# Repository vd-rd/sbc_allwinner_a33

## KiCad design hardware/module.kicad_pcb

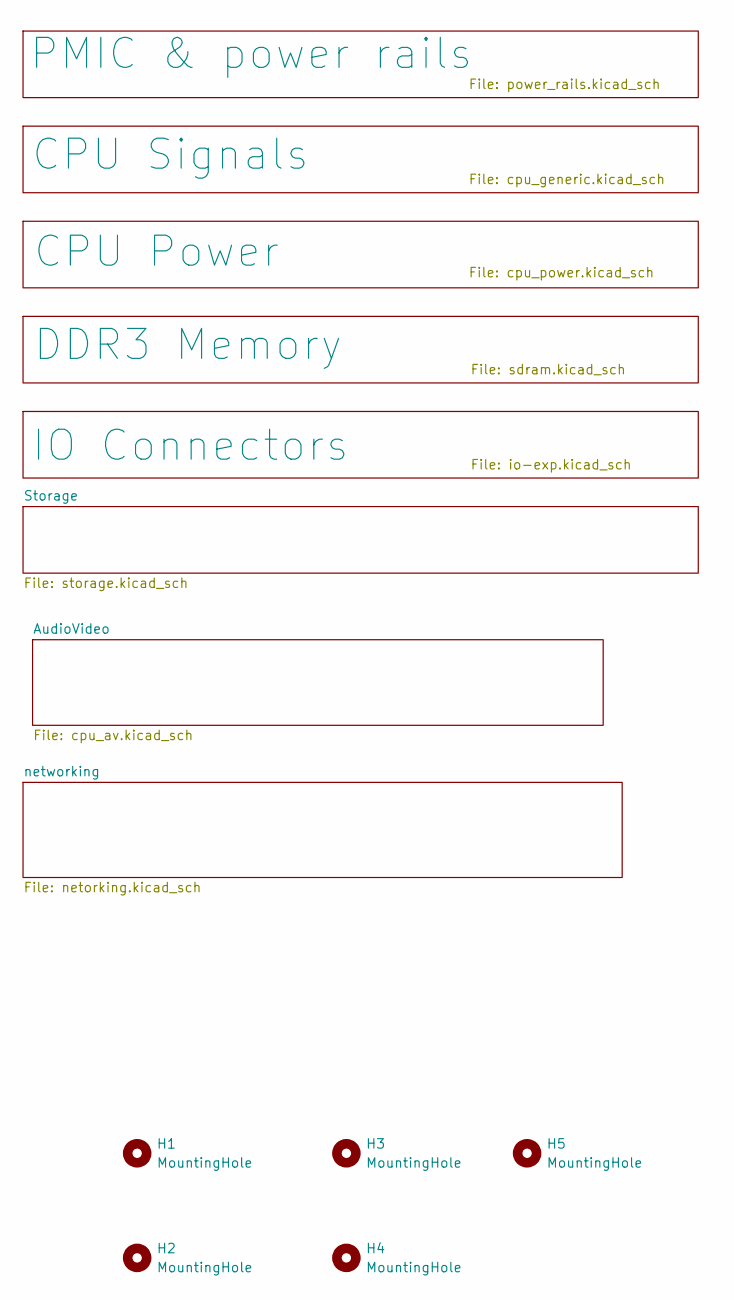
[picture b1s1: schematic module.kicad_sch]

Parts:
H1, H2, H3, H4, H5: MountingHole; MountingHole_2.7mm_M2.5_DIN965

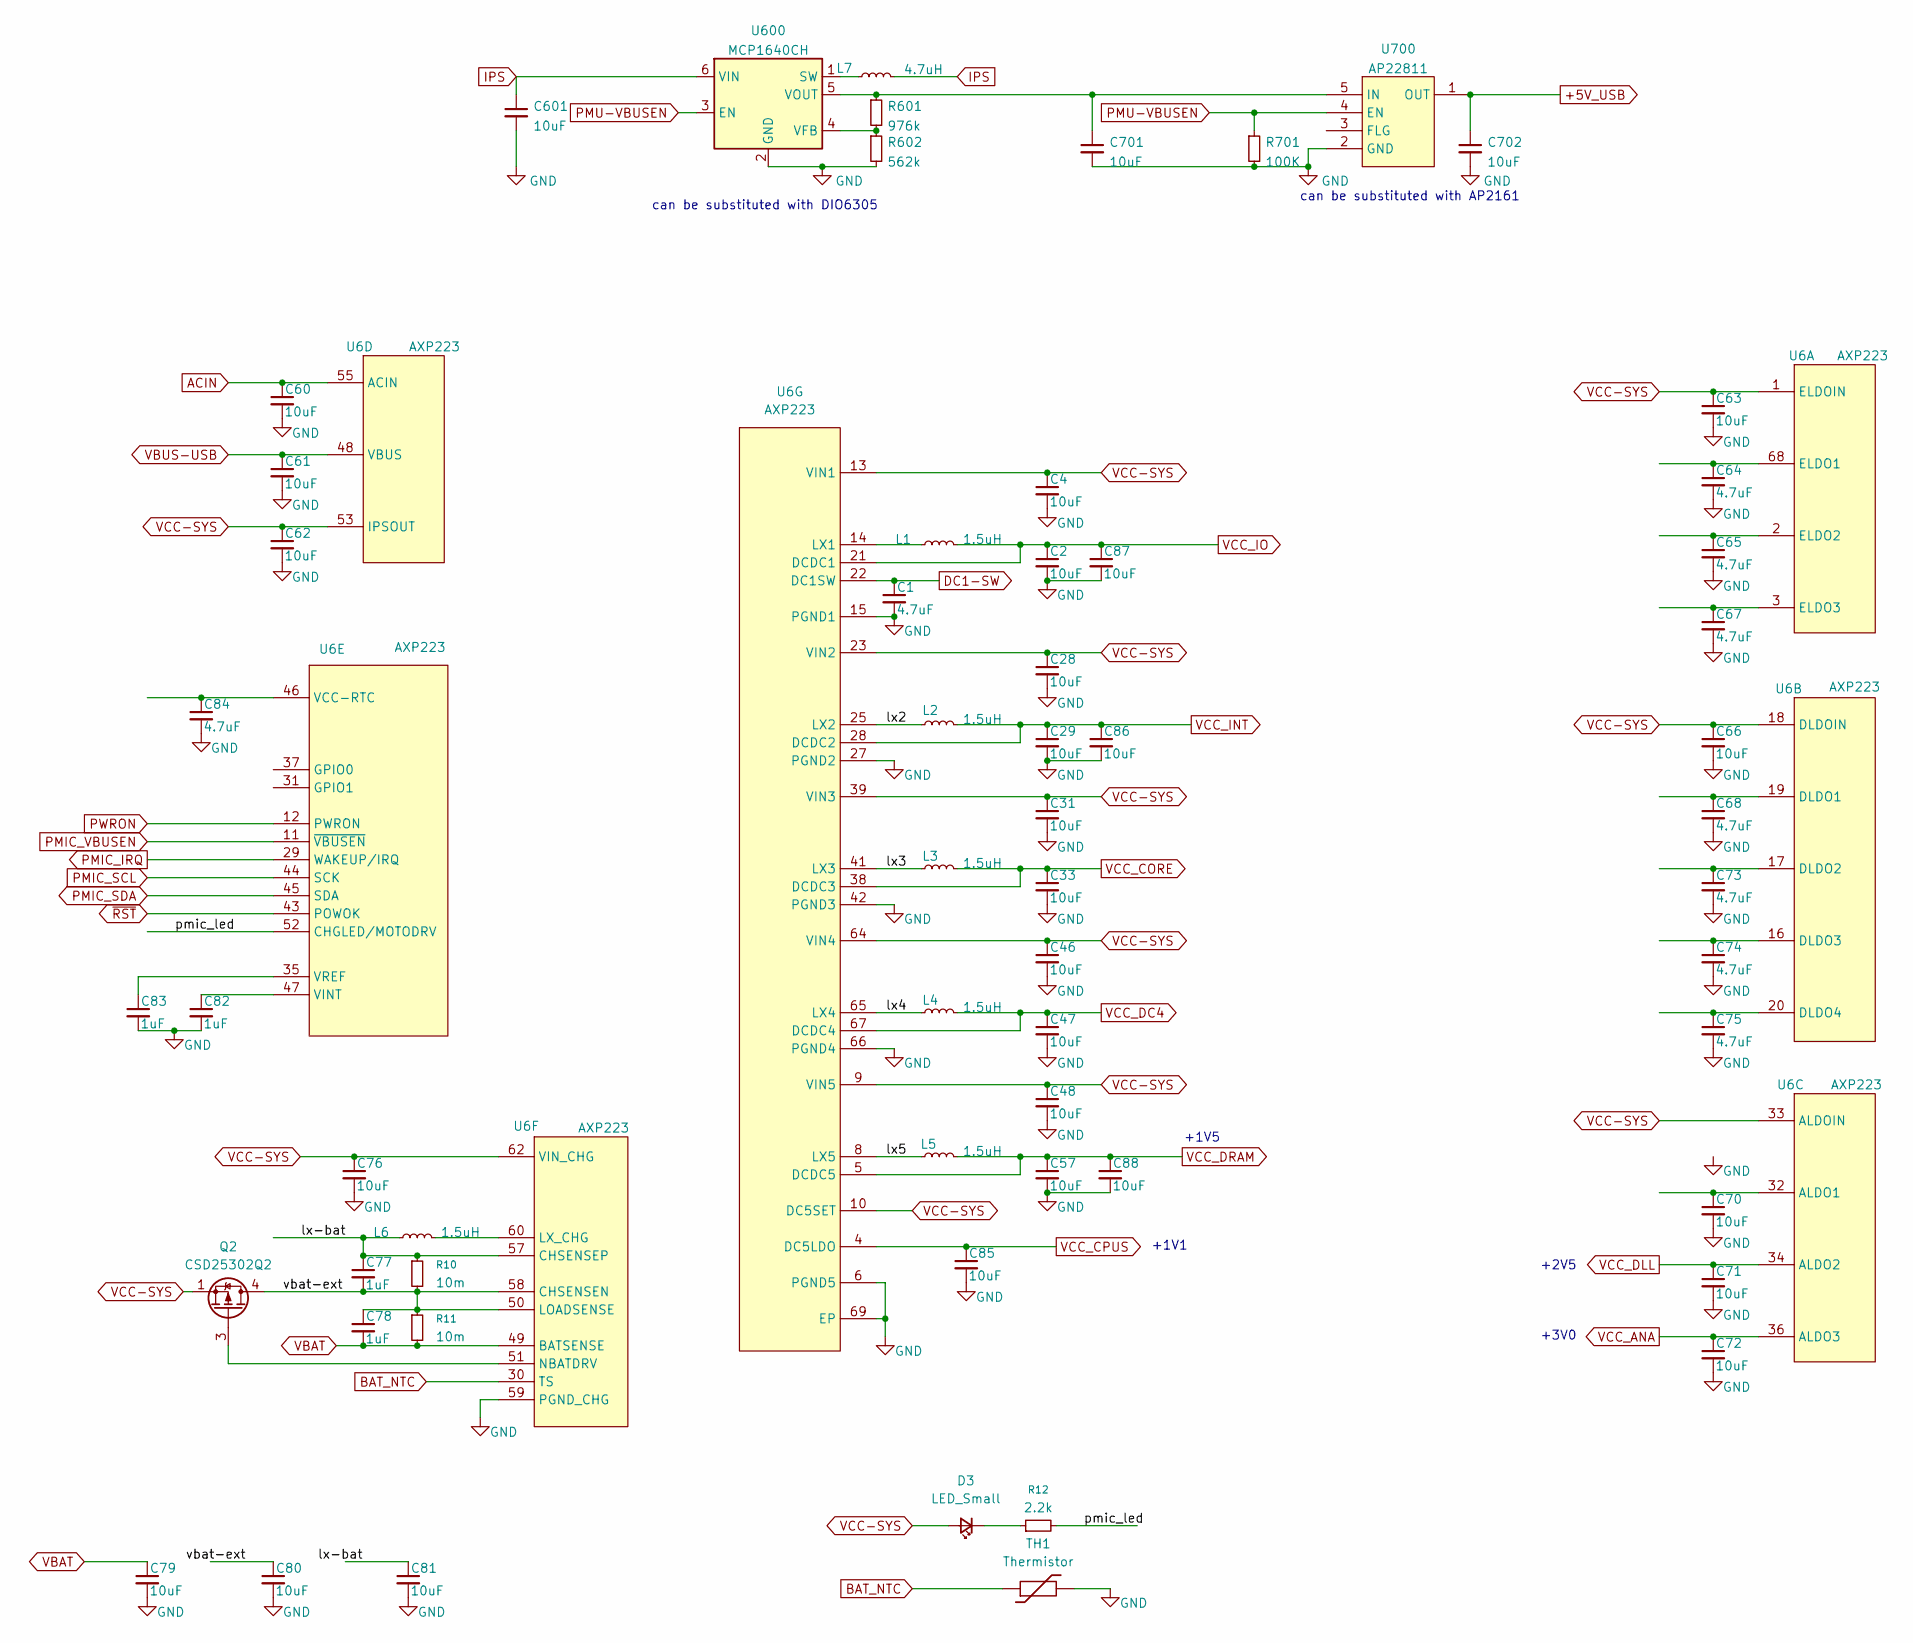
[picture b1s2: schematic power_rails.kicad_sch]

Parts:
C1, C64, C65, C67, C68, C73, C74, C75, C84: 4.7uF; C_0402_1005Metric
C2, C4, C28, C29, C31, C33, C46, C47, C48, C57, C60, C61, C62, C63, C66, C70, C71, C72, C76, C79, C80, C81, C85, C86, C87, C88, C601, C701, C702: 10uF; C_0603_1608Metric
C77, C78, C82, C83: 1uF; C_0402_1005Metric
D3: LED_Small; LED_0603_1608Metric
L1, L2, L3, L4, L5, L6: 1.5uH; L_APV_ANR252010
L7: 4.7uH; L_Wuerth_MAPI-2510
Q2: CSD25302Q2; Texas_DQK
R10, R11: 10m; R_0805_2012Metric
R12: 2.2k; R_0402_1005Metric
R601: 976k; R_0402_1005Metric
R602: 562k; R_0402_1005Metric
R701: 100K; R_0402_1005Metric
TH1: Thermistor; R_0603_1608Metric
U6: AXP223; QFN-68-1EP_8x8mm_P0.4mm_EP5.5x5.5mm_ThermalVias
U600: MCP1640CH; SOT-23-6
U700: AP22811; SOT-23-5

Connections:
+5V_USB: C702.1, U700.1 (OUT); also elsewhere on the board
/PMIC & power rails/lx2: L2.1, U6.24 (LX2), U6.25 (LX2)
/PMIC & power rails/lx3: L3.1, U6.40 (LX3), U6.41 (LX3)
/PMIC & power rails/lx4: L4.1, U6.65 (LX4)
/PMIC & power rails/lx5: L5.1, U6.7 (LX5), U6.8 (LX5)
/PMIC & power rails/lx-bat: C77.1, C81.1, L6.1, R10.1, U6.57 (CHSENSEP)
/PMIC & power rails/pmic_led: R12.2, U6.52 (CHGLED/MOTODRV)
/PMIC & power rails/vbat-ext: C77.2, C78.1, C80.1, Q2.4 (D), Q2.7 (D), R10.2, R11.1, U6.50 (LOADSENSE), U6.58 (CHSENSEN)
ACIN: C60.1, U6.55 (ACIN), U6.56 (ACIN); also elsewhere on the board
BAT_NTC: TH1.1, U6.30 (TS); also elsewhere on the board
DC1-SW: C1.1, U6.22 (DC1SW)
GND: C1.2, C2.2, C4.2, C28.2, C29.2, C31.2, C33.2, C46.2, C47.2, C48.2, C57.2, C60.2, C61.2, C62.2, C63.2, C64.2, C65.2, C66.2, C67.2, C68.2, C70.2, C71.2, C72.2, C73.2, C74.2, C75.2, C76.2, C79.2, C80.2, C81.2, C82.2, C83.2, C84.2, C85.2, C86.2, C87.2, C88.2, C601.2, C701.2, C702.2, R602.2, R701.2, TH1.2, U6.6 (PGND5), U6.15 (PGND1), U6.26 (PGND2), U6.27 (PGND2), U6.42 (PGND3), U6.59 (PGND_CHG), U6.66 (PGND4), U6.69 (EP), U600.2 (GND), U700.2 (GND); also elsewhere on the board
IPS: C601.1, L7.2, U600.6 (VIN)
unnamed: D3.1 (K), R12.1
unnamed: L6.2, U6.60 (LX_CHG), U6.61 (LX_CHG)
unnamed: Q2.3 (G), U6.51 (NBATDRV)
unnamed: C64.1, U6.68 (ELDO1)
unnamed: C65.1, U6.2 (ELDO2)
unnamed: C67.1, U6.3 (ELDO3)
unnamed: C68.1, U6.19 (DLDO1)
unnamed: C73.1, U6.17 (DLDO2)
unnamed: C74.1, U6.16 (DLDO3)
unnamed: C75.1, U6.20 (DLDO4)
unnamed: C70.1, U6.32 (ALDO1)
unnamed: C84.1, U6.46 (VCC-RTC)
unnamed: C82.1, U6.47 (VINT)
unnamed: C83.1, U6.35 (VREF)
unnamed: L1.1, U6.14 (LX1)
unnamed: L7.1, U600.1 (SW)
unnamed: R601.2, R602.1, U600.4 (VFB)
unnamed: C701.1, R601.1, U600.5 (VOUT), U700.5 (IN)
PMIC_IRQ: U6.29 (WAKEUP/IRQ); also elsewhere on the board
PMIC_SCL: U6.44 (SCK); also elsewhere on the board
PMIC_SDA: U6.45 (SDA); also elsewhere on the board
PMIC_VBUSEN: U6.11 (~VBUSEN)
PMU-VBUSEN: R701.1, U600.3 (EN), U700.4 (EN)
PWRON: U6.12 (PWRON); also elsewhere on the board
VBAT: C78.2, C79.1, R11.2, U6.49 (BATSENSE); also elsewhere on the board
VBUS-USB: C61.1, U6.48 (VBUS)
VCC-SYS: C4.1, C28.1, C31.1, C46.1, C48.1, C62.1, C63.1, C66.1, C76.1, D3.2 (A), Q2.1 (S), Q2.2 (S), Q2.5 (S), Q2.6 (S), Q2.8 (S), U6.1 (ELDOIN), U6.9 (VIN5), U6.10 (DC5SET), U6.13 (VIN1), U6.18 (DLDOIN), U6.23 (VIN2), U6.33 (ALDOIN), U6.39 (VIN3), U6.53 (IPSOUT), U6.54 (IPSOUT), U6.62 (VIN_CHG), U6.63 (VIN_CHG), U6.64 (VIN4)
VCC_ANA: C72.1, U6.36 (ALDO3); also elsewhere on the board
VCC_CORE: C33.1, L3.2, U6.38 (DCDC3); also elsewhere on the board
VCC_CPUS: C85.1, U6.4 (DC5LDO); also elsewhere on the board
VCC_DC4: C47.1, L4.2, U6.67 (DCDC4)
VCC_DLL: C71.1, U6.34 (ALDO2); also elsewhere on the board
VCC_DRAM: C57.1, C88.1, L5.2, U6.5 (DCDC5); also elsewhere on the board
VCC_INT: C29.1, C86.1, L2.2, U6.28 (DCDC2); also elsewhere on the board
VCC_IO: C2.1, C87.1, L1.2, U6.21 (DCDC1); also elsewhere on the board
~RST: U6.43 (POWOK); also elsewhere on the board

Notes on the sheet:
can be substituted with DIO6305
can be substituted with AP2161
+1V1
+2V5
+1V5
+3V0

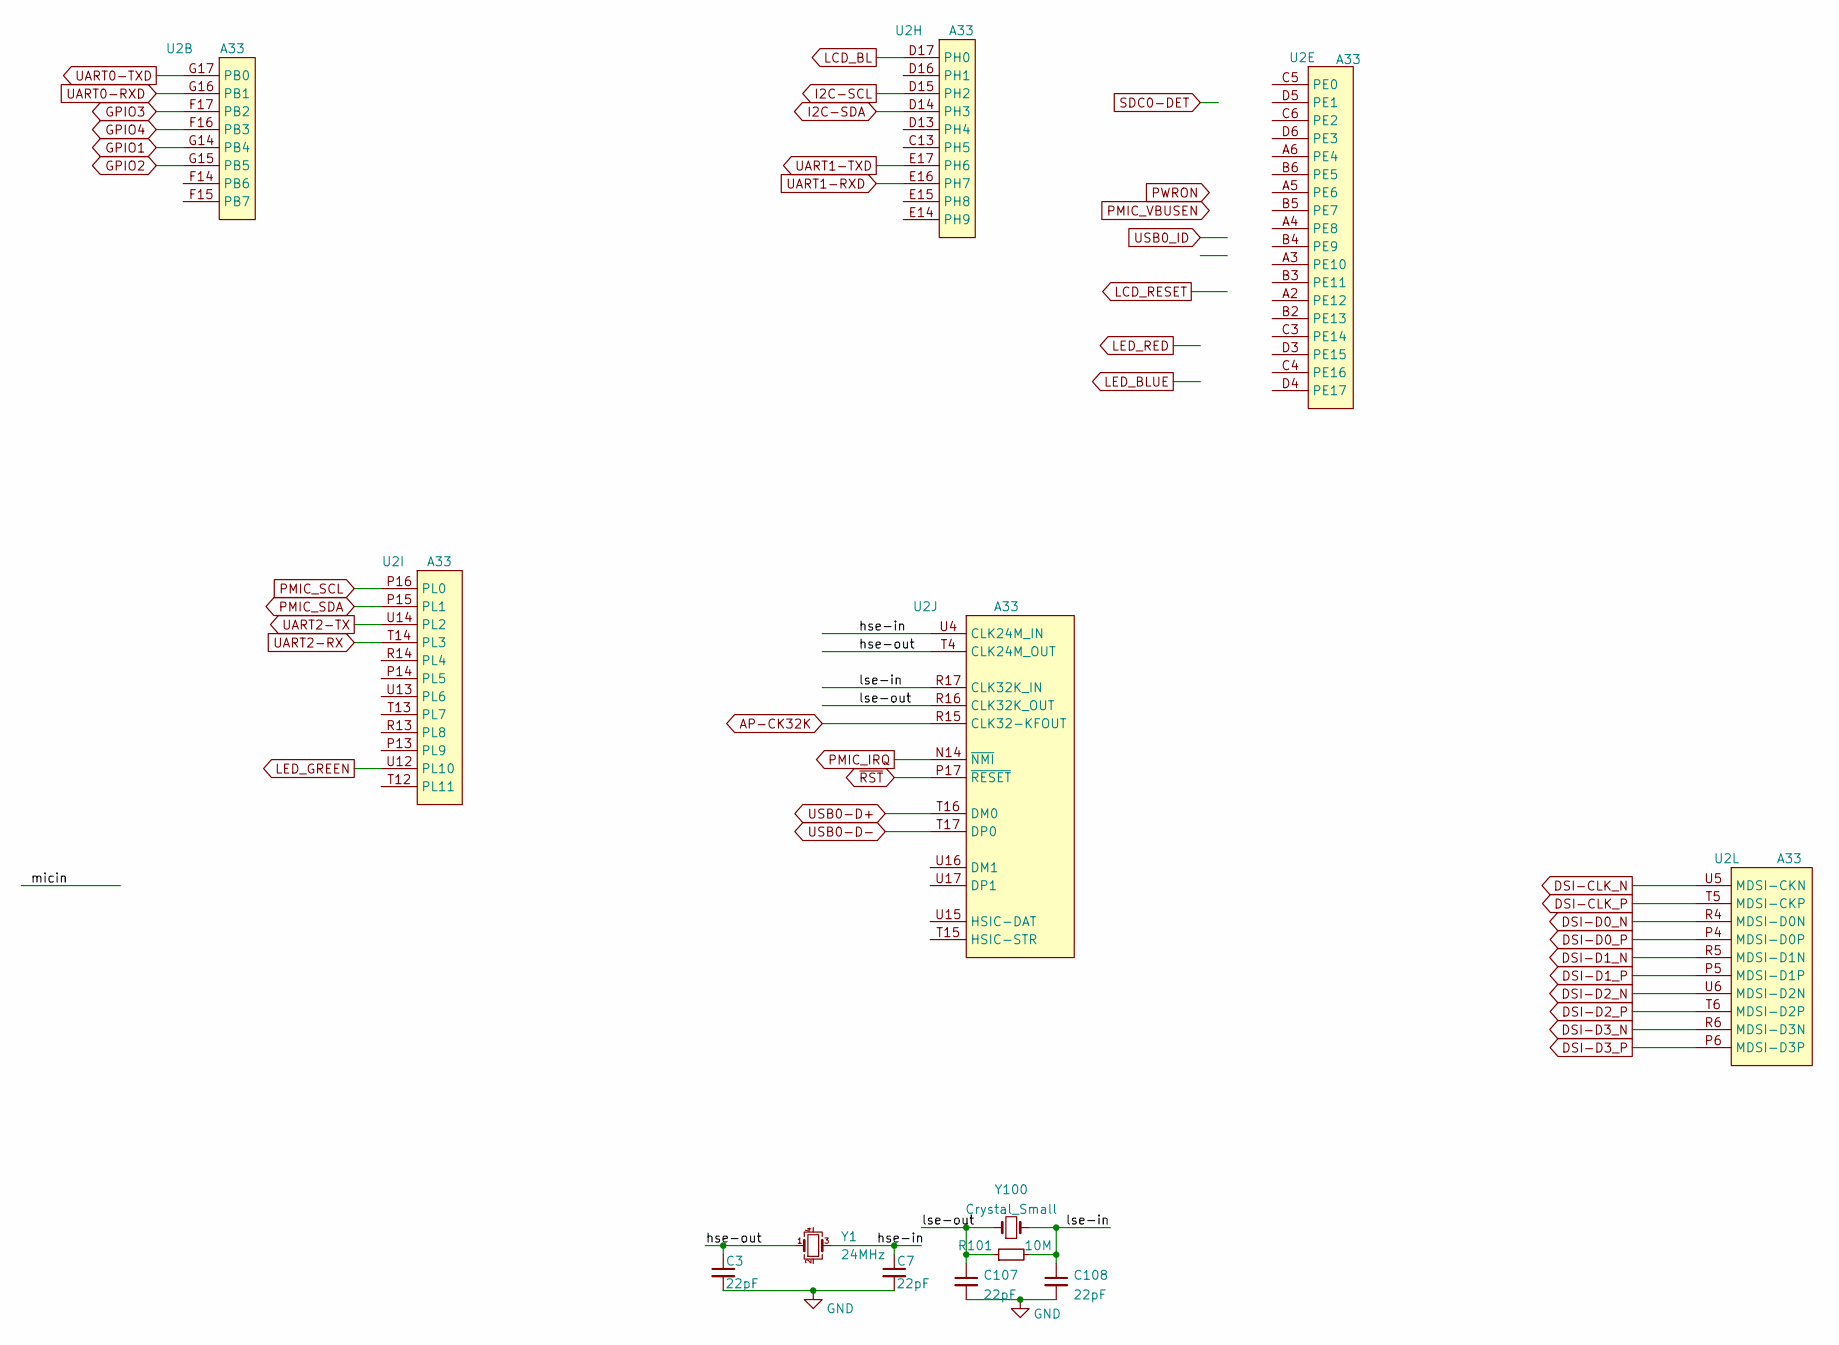
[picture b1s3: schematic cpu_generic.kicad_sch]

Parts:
C3, C7, C107, C108: 22pF; C_0402_1005Metric
R101: 10M; R_0402_1005Metric
U2: A33; BGA-282_17x17_14.0x14.0mm
Y1: 24MHz; Crystal_SMD_3225-4Pin_3.2x2.5mm
Y100: Crystal_Small; Crystal_SMD_3215-2Pin_3.2x1.5mm

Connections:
/CPU Signals/hse-in: C7.1, U2.U4 (CLK24M_IN), Y1.3
/CPU Signals/hse-out: C3.1, U2.T4 (CLK24M_OUT), Y1.1
/CPU Signals/lse-in: C108.1, R101.2, U2.R17 (CLK32K_IN), Y100.2
/CPU Signals/lse-out: C107.1, R101.1, U2.R16 (CLK32K_OUT), Y100.1
AP-CK32K: U2.R15 (CLK32-KFOUT); also elsewhere on the board
DSI-CLK_N: U2.U5 (MDSI-CKN)
DSI-CLK_P: U2.T5 (MDSI-CKP)
DSI-D0_N: U2.R4 (MDSI-D0N)
DSI-D0_P: U2.P4 (MDSI-D0P)
DSI-D1_N: U2.R5 (MDSI-D1N)
DSI-D1_P: U2.P5 (MDSI-D1P)
DSI-D2_N: U2.U6 (MDSI-D2N)
DSI-D2_P: U2.T6 (MDSI-D2P)
DSI-D3_N: U2.R6 (MDSI-D3N)
DSI-D3_P: U2.P6 (MDSI-D3P)
GND: C3.2, C7.2, C107.2, C108.2; also elsewhere on the board
GPIO1: U2.G14 (PB4); also elsewhere on the board
GPIO2: U2.G15 (PB5); also elsewhere on the board
GPIO3: U2.F17 (PB2); also elsewhere on the board
GPIO4: U2.F16 (PB3); also elsewhere on the board
I2C-SCL: U2.D15 (PH2); also elsewhere on the board
I2C-SDA: U2.D14 (PH3); also elsewhere on the board
LCD_BL: U2.D17 (PH0); also elsewhere on the board
LED_GREEN: U2.U12 (PL10); also elsewhere on the board
PMIC_IRQ: U2.N14 (~NMI); also elsewhere on the board
PMIC_SCL: U2.P16 (PL0); also elsewhere on the board
PMIC_SDA: U2.P15 (PL1); also elsewhere on the board
UART0-RXD: U2.G16 (PB1); also elsewhere on the board
UART0-TXD: U2.G17 (PB0); also elsewhere on the board
UART1-RXD: U2.E16 (PH7); also elsewhere on the board
UART1-TXD: U2.E17 (PH6); also elsewhere on the board
UART2-RX: U2.T14 (PL3); also elsewhere on the board
UART2-TX: U2.U14 (PL2); also elsewhere on the board
USB0-D+: U2.T16 (DM0); also elsewhere on the board
USB0-D-: U2.T17 (DP0); also elsewhere on the board
~RST: U2.P17 (~RESET); also elsewhere on the board

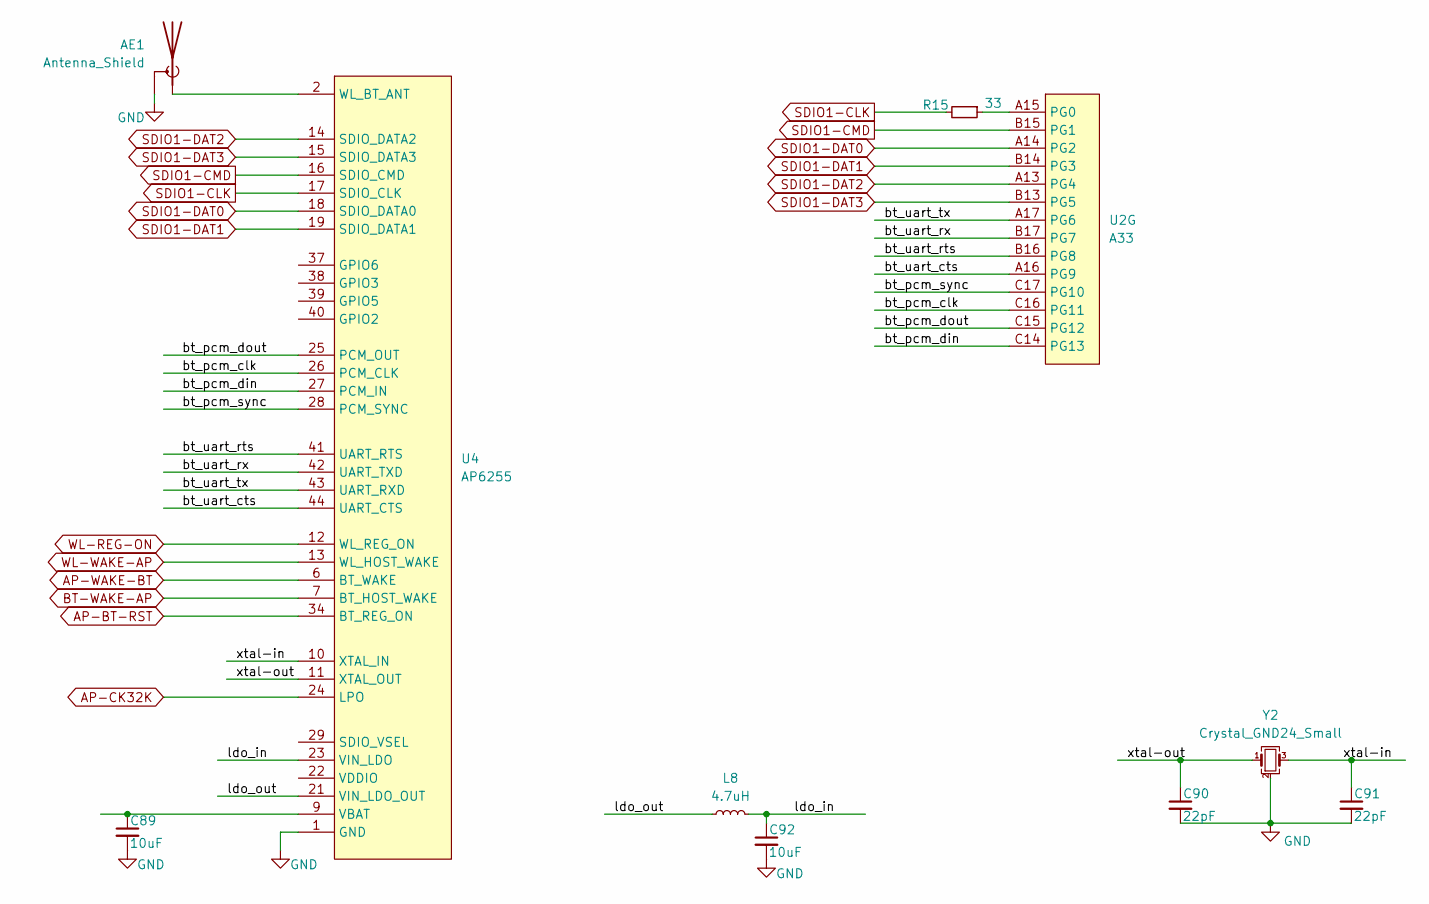
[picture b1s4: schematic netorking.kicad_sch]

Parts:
AE1: Antenna_Shield; U.FL_Hirose_U.FL-R-SMT-1_Vertical
C89, C92: 10uF; C_0603_1608Metric
C90, C91: 22pF; C_0402_1005Metric
L8: 4.7uH; L_APV_ANR252010
R15: 33; R_0402_1005Metric
U2: A33; BGA-282_17x17_14.0x14.0mm
U4: AP6255; lga44_12x12mm_P0.9
Y2: Crystal_GND24_Small; Crystal_SMD_3225-4Pin_3.2x2.5mm

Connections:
/networking/bt_pcm_clk: U2.C16 (PG11), U4.26 (PCM_CLK)
/networking/bt_pcm_din: U2.C14 (PG13), U4.27 (PCM_IN)
/networking/bt_pcm_dout: U2.C15 (PG12), U4.25 (PCM_OUT)
/networking/bt_pcm_sync: U2.C17 (PG10), U4.28 (PCM_SYNC)
/networking/bt_uart_cts: U2.A16 (PG9), U4.44 (UART_CTS)
/networking/bt_uart_rts: U2.B16 (PG8), U4.41 (UART_RTS)
/networking/bt_uart_rx: U2.B17 (PG7), U4.42 (UART_TXD)
/networking/bt_uart_tx: U2.A17 (PG6), U4.43 (UART_RXD)
/networking/ldo_in: C92.1, L8.2, U4.23 (VIN_LDO)
/networking/ldo_out: L8.1, U4.21 (VIN_LDO_OUT)
/networking/xtal-in: C91.1, U4.10 (XTAL_IN), Y2.3
/networking/xtal-out: C90.1, U4.11 (XTAL_OUT), Y2.1
AP-BT-RST: U4.34 (BT_REG_ON)
AP-CK32K: U4.24 (LPO); also elsewhere on the board
AP-WAKE-BT: U4.6 (BT_WAKE)
BT-WAKE-AP: U4.7 (BT_HOST_WAKE)
GND: AE1.2 (Shield), C89.2, C90.2, C91.2, C92.2, U4.1 (GND), U4.3 (GND), U4.20 (GND), U4.31 (GND), U4.33 (GND), U4.36 (GND), Y2.2 (G), Y2.4 (G); also elsewhere on the board
unnamed: AE1.1 (A), U4.2 (WL_BT_ANT)
unnamed: R15.1, U2.A15 (PG0)
unnamed: C89.1, U4.9 (VBAT)
SDIO1-CLK: R15.2, U4.17 (SDIO_CLK)
SDIO1-CMD: U2.B15 (PG1), U4.16 (SDIO_CMD)
SDIO1-DAT0: U2.A14 (PG2), U4.18 (SDIO_DATA0)
SDIO1-DAT1: U2.B14 (PG3), U4.19 (SDIO_DATA1)
SDIO1-DAT2: U2.A13 (PG4), U4.14 (SDIO_DATA2)
SDIO1-DAT3: U2.B13 (PG5), U4.15 (SDIO_DATA3)
WL-REG-ON: U4.12 (WL_REG_ON)
WL-WAKE-AP: U4.13 (WL_HOST_WAKE)

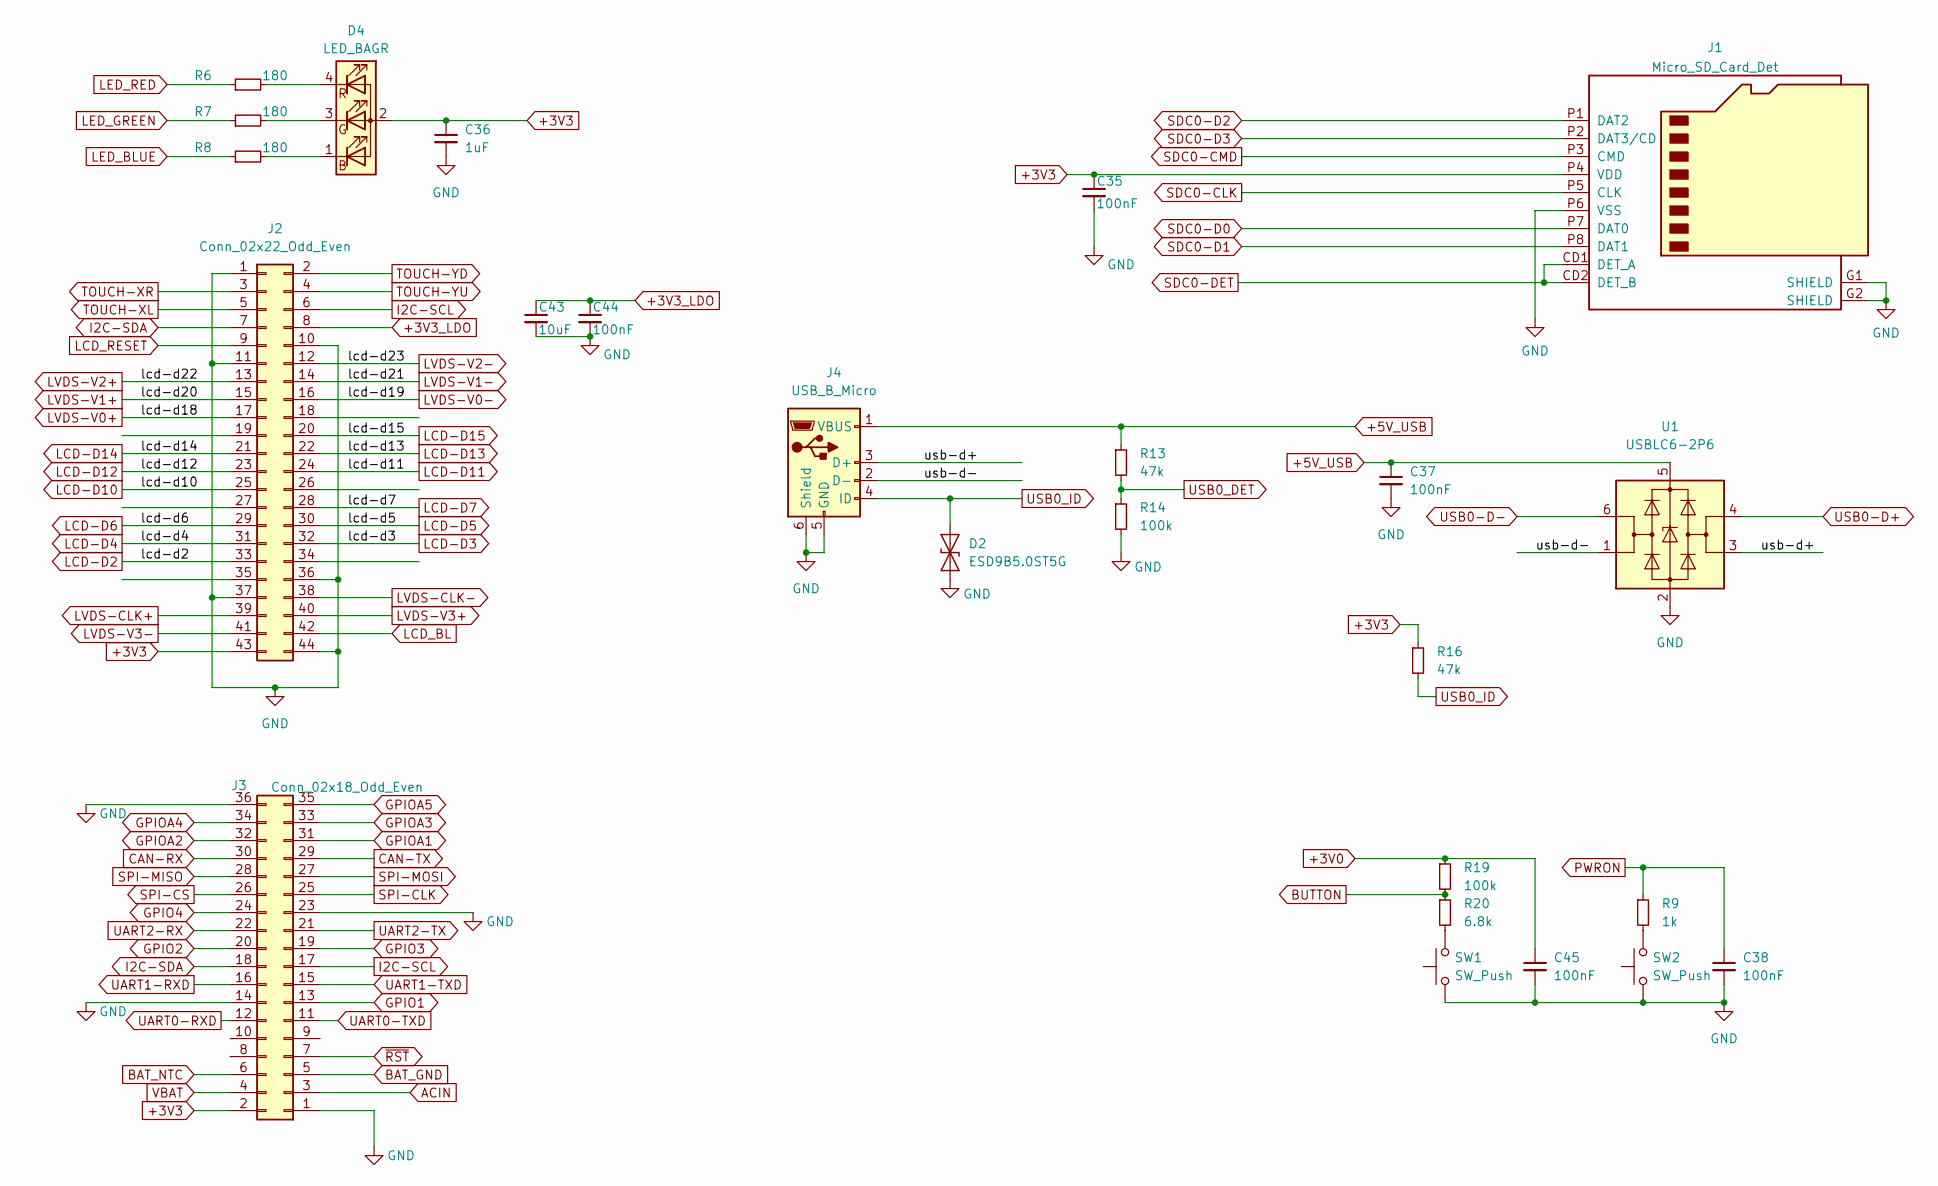
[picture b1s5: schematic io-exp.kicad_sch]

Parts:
C35, C37, C38, C44, C45: 100nF; C_0402_1005Metric
C36: 1uF; C_0402_1005Metric
C43: 10uF; C_0603_1608Metric
D2: ESD9B5.0ST5G; D_SOD-923
D4: LED_BAGR; LED_RGB_Optosupply_OSTB0805C1E-A-0.8T
J1: Micro_SD_Card_Det; MEM20610118800A
J2: Conn_02x22_Odd_Even; PinHeader_2x22_P1.27mm_Vertical
J3: Conn_02x18_Odd_Even; PinHeader_2x18_P2.54mm_Vertical
J4: USB_B_Micro; USB_Micro-B_Amphenol_10103594-0001LF_Horizontal
R6, R7, R8: 180; R_0402_1005Metric
R9: 1k; R_0402_1005Metric
R13, R16: 47k; R_0402_1005Metric
R14, R19: 100k; R_0402_1005Metric
R20: 6.8k; R_0402_1005Metric
SW1, SW2: SW_Push; SW_SPST_EVQP7C
U1: USBLC6-2P6; SOT-23-6

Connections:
+3V0: C45.1, R19.1
+3V3: C35.1, C36.1, D4.2 (A), J1.P4 (VDD), J2.43, J3.2, R16.1
+3V3_LDO: C43.1, C44.1, J2.8
+5V_USB: C37.1, J4.1 (VBUS), R13.1, U1.5 (VBUS); also elsewhere on the board
/IO Connectors/usb-d+: J4.3 (D+), U1.3 (I/O2)
/IO Connectors/usb-d-: J4.2 (D-), U1.1 (I/O1)
ACIN: J3.3; also elsewhere on the board
BAT_GND: J3.5
BAT_NTC: J3.6; also elsewhere on the board
BUTTON: R19.2, R20.1; also elsewhere on the board
CAN-RX: J3.30
CAN-TX: J3.29
GND: C35.2, C36.2, C37.2, C38.2, C43.2, C44.2, C45.2, D2.2 (A2), J1.G1 (SHIELD), J1.G2 (SHIELD), J1.P6 (VSS), J2.1, J2.10, J2.11, J2.36, J2.37, J2.44, J3.1, J3.14, J3.23, J3.36, J4.5 (GND), J4.6 (Shield), R14.2, SW1.1, SW2.1, U1.2 (GND); also elsewhere on the board
GPIO1: J3.13; also elsewhere on the board
GPIO2: J3.20; also elsewhere on the board
GPIO3: J3.19; also elsewhere on the board
GPIO4: J3.24; also elsewhere on the board
GPIOA1: J3.31
GPIOA2: J3.32
GPIOA3: J3.33
GPIOA4: J3.34
GPIOA5: J3.35
I2C-SCL: J2.6, J3.17; also elsewhere on the board
I2C-SDA: J2.7, J3.18; also elsewhere on the board
LCD-D2: J2.33; also elsewhere on the board
LCD-D3: J2.32; also elsewhere on the board
LCD-D4: J2.31; also elsewhere on the board
LCD-D5: J2.30; also elsewhere on the board
LCD-D6: J2.29; also elsewhere on the board
LCD-D7: J2.28; also elsewhere on the board
LCD-D10: J2.25; also elsewhere on the board
LCD-D11: J2.24; also elsewhere on the board
LCD-D12: J2.23; also elsewhere on the board
LCD-D13: J2.22; also elsewhere on the board
LCD-D14: J2.21; also elsewhere on the board
LCD-D15: J2.20; also elsewhere on the board
LCD_BL: J2.42; also elsewhere on the board
LCD_RESET: J2.9
LED_BLUE: R8.1
LED_GREEN: R7.1; also elsewhere on the board
LED_RED: R6.1
LVDS-CLK+: J2.39; also elsewhere on the board
LVDS-CLK-: J2.38; also elsewhere on the board
LVDS-V0+: J2.17; also elsewhere on the board
LVDS-V0-: J2.16; also elsewhere on the board
LVDS-V1+: J2.15; also elsewhere on the board
LVDS-V1-: J2.14; also elsewhere on the board
LVDS-V2+: J2.13; also elsewhere on the board
LVDS-V2-: J2.12; also elsewhere on the board
LVDS-V3+: J2.40; also elsewhere on the board
LVDS-V3-: J2.41; also elsewhere on the board
unnamed: D4.1 (BK), R8.2
unnamed: D4.3 (GK), R7.2
unnamed: D4.4 (RK), R6.2
unnamed: R9.2, SW2.2
unnamed: R20.2, SW1.2
PWRON: C38.1, R9.1; also elsewhere on the board
SDC0-CLK: J1.P5 (CLK); also elsewhere on the board
SDC0-CMD: J1.P3 (CMD); also elsewhere on the board
SDC0-D0: J1.P7 (DAT0); also elsewhere on the board
SDC0-D1: J1.P8 (DAT1); also elsewhere on the board
SDC0-D2: J1.P1 (DAT2); also elsewhere on the board
SDC0-D3: J1.P2 (DAT3/CD); also elsewhere on the board
SDC0-DET: J1.CD1 (DET_A), J1.CD2 (DET_B)
SPI-CLK: J3.25; also elsewhere on the board
SPI-CS: J3.26
SPI-MISO: J3.28; also elsewhere on the board
SPI-MOSI: J3.27; also elsewhere on the board
TOUCH-XL: J2.5
TOUCH-XR: J2.3
TOUCH-YD: J2.2
TOUCH-YU: J2.4
UART0-RXD: J3.12; also elsewhere on the board
UART0-TXD: J3.11; also elsewhere on the board
UART1-RXD: J3.16; also elsewhere on the board
UART1-TXD: J3.15; also elsewhere on the board
UART2-RX: J3.22; also elsewhere on the board
UART2-TX: J3.21; also elsewhere on the board
USB0-D+: U1.4 (I/O2); also elsewhere on the board
USB0-D-: U1.6 (I/O1); also elsewhere on the board
USB0_DET: R13.2, R14.1
USB0_ID: D2.1 (A1), J4.4 (ID), R16.2
VBAT: J3.4; also elsewhere on the board
~RST: J3.7; also elsewhere on the board

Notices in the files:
hardware/module.kicad_pcb:
© VDRD 2022
